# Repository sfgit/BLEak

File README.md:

BLEak
=====

BLE + ATMega Kit

Meet BLEak - the BLE + ATMega Kit.  This is a board I'm building for a one-day workshop in San Francisco.  The board includes the NRF8001 + ATMega328-AUR (SMD, a'la Arduino SMD) and should include some basic SPI sensors / IO.  Existing Arduino SW libraries for the nrf8001 should work with BLEak.  The basis of the workshop is to show the transition from Arduino to a production PCB and BLEak is a nice narrative that mixes some simple wireless / RF with the ATMega in a module that just might be the prodcut someone is trying to build.  

LICENSE + NOTES:  (PLEASE READ)
This design is released under a Creative-Commons Share-alike, Attribution license.  You can use this design without needing to ask for permission from me.

The designer (me, the guy typing this) is furnishing this item "as is". The design does not provide any warranty of the item whatsoever, whether express, implied, or statutory, including, but not limited to, any warranty of merchantability or fitness for a particular purpose or any warranty that the contents of the item will be error-free.

In no respect shall the designer incur any liability for any damages, including, but limited to, direct, indirect, special, or consequential damages arising out of, resulting from, or any way connected to the use of the item, whether or not based upon warranty, contract, tort, or otherwise; whether or not injury was sustained by persons or property or otherwise; and whether or not loss was sustained from, or arose out of, the results of, the item, or any services that may be provided by the designer.

Be careful.  This is a work in progress.  You use this AT YOUR OWN RISK.  Electronics such as these can kill.

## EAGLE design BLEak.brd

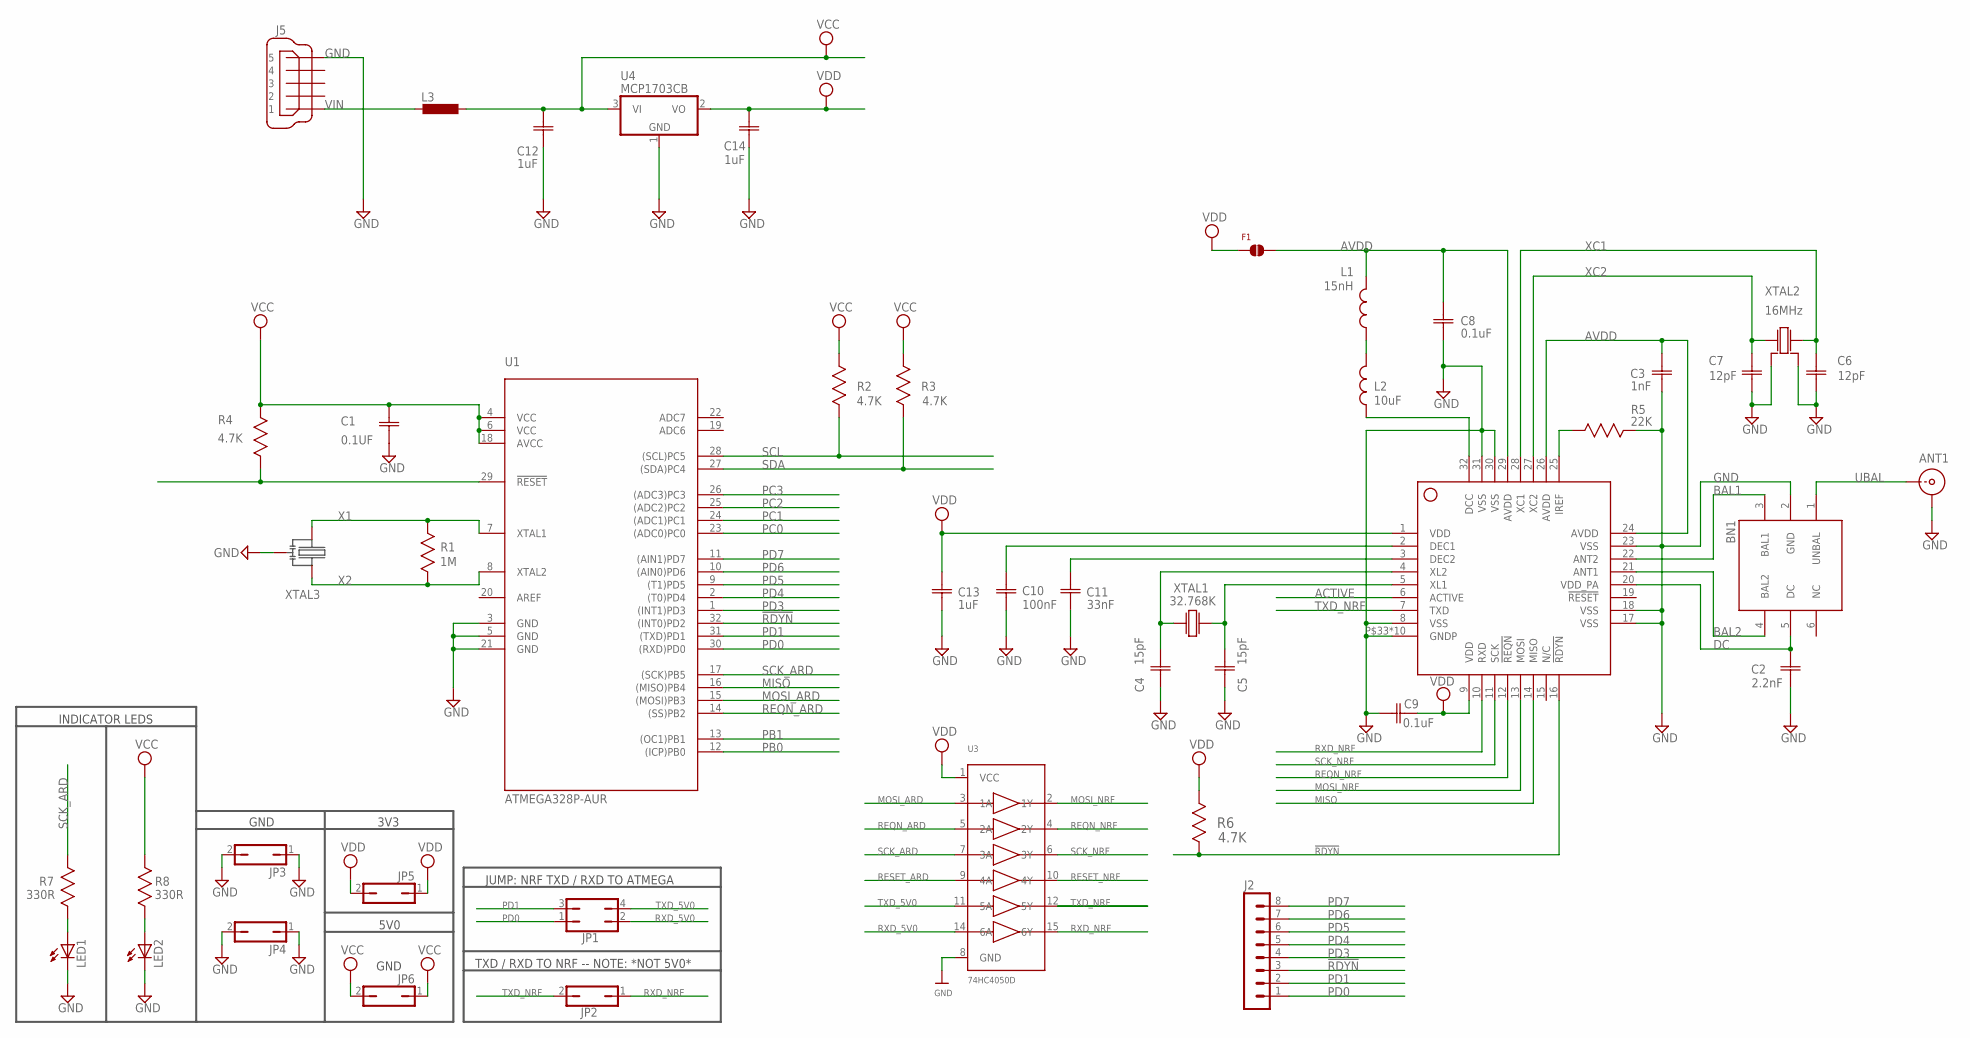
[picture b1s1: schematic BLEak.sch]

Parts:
ANT1: U.FL-R-SMT(01); U.FL; PARTNO U.FL-R-SMT(01)
BN1: 2450BM14A0002; BALUN; PARTNO 2450BM14A0002
C1: 0.1UF; CAPC1608X90N
C2: 2.2nF; CAPC1608X85N
C3: 1nF; CAPC1608X85N
C4, C5: 15pF; CAPC1608X85N
C6, C7: 12pF; CAPC1608X85N
C8, C9: 0.1uF; CAPC1608X90N
C10: 100nF; CAPC1608X90N
C11: 33nF; CAPC1608X85N
C12, C14: 1uF; CAPC2013X140N
C13: 1uF; CAPC1608X90N
F1: MMZ1608B121C; 0603
J2: MA08-1
J5: MINI-USB-UX60A-MB-5ST; UX60A-MB-5ST
JP1: JP2Q
JP2, JP3, JP4, JP5, JP6: JP1Q; JP1
L1: 15nH; 0402
L2: 10uF; 0603
L3: L-EUL1812; L1812
LED1, LED2: LEDCHIP-LED0603; CHIP-LED0603
R1: 1M; RESC1608X60N
R2, R3, R4, R6: 4.7K; RESC1608X60N
R5: 22K; RESC1608X60N
R7, R8: 330R; RESC1608X60N
U1: ATMEGA328P-AUR; TQFP-32; PARTNO ATMEGA328P-AUR
U2: NRF8001; QFN50P500X500X90-33N; PARTNO nRF8001
U3: 74HC4050D; TSSOP16
U4: MCP1703CB; SOT23
XTAL1: 32.768K; 3215
XTAL2: 16MHz; 3225
XTAL3: CSTCE16M0V53-R0

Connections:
!RDYN: J2.3, R6.2 (R2), U1.32 ((INT0)PD2), U2.16 (!RDYN)
ACTIVE: U2.6 (ACTIVE)
AVDD: C3.2 (C2), C8.2 (C2), F1.P$2 (2), L1.P$2, U2.24 (AVDD), U2.26 (AVDD), U2.29 (AVDD)
BAL1: BN1.3 (BAL1), U2.22 (ANT2)
BAL2: BN1.4 (BAL2), U2.21 (ANT1)
DC: BN1.5 (DC), C2.2 (C2), U2.20 (VDD_PA)
GND: ANT1.2, ANT1.3, BN1.2 (GND), C1.1 (C1), C2.1 (C1), C3.1 (C1), C4.1 (C1), C5.1 (C1), C6.1 (C1), C7.1 (C1), C8.1 (C1), C9.2 (C2), C10.1 (C1), C11.2 (C2), C12.1 (C1), C13.1 (C1), C14.1 (C1), J5.5, JP3.1, JP3.2, JP4.1, JP4.2, LED1.C, LED2.C, R5.1 (R1), U1.3 (GND), U1.5 (GND), U1.21 (GND), U2.8 (VSS), U2.17 (VSS), U2.18 (VSS), U2.23 (VSS), U2.30 (VSS), U2.31 (VSS), U2.P$33 (GNDP), U2.P$34 (GNDP), U2.P$35 (GNDP), U2.P$36 (GNDP), U2.P$37 (GNDP), U2.P$38 (GNDP), U2.P$39 (GNDP), U2.P$40 (GNDP), U2.P$41 (GNDP), U2.P$42 (GNDP), U3.8 (GND), U4.1 (GND), XTAL2.2, XTAL2.4, XTAL3.2
MISO: U1.16 ((MISO)PB4), U2.14 (MISO)
MOSI_ARD: U1.15 ((MOSI)PB3), U3.3 (1A)
MOSI_NRF: U2.13 (MOSI), U3.2 (1Y)
unnamed: R4.2 (R2), U1.29 (!RESET)
unnamed: R5.2 (R2), U2.25 (IREF)
unnamed: C4.2 (C2), U2.4 (XL2), XTAL1.2
unnamed: C5.2 (C2), U2.5 (XL1), XTAL1.1
unnamed: L1.P$1, L2.2
unnamed: L2.1, U2.32 (DCC)
unnamed: C11.1 (C1), U2.3 (DEC2)
unnamed: C10.2 (C2), U2.2 (DEC1)
unnamed: LED2.A, R8.2 (R2)
unnamed: LED1.A, R7.2 (R2)
PB0: U1.12 ((ICP)PB0)
PB1: U1.13 ((OC1)PB1)
PC0: U1.23 ((ADC0)PC0)
PC1: U1.24 ((ADC1)PC1)
PC2: U1.25 ((ADC2)PC2)
PC3: U1.26 ((ADC3)PC3)
PD0: J2.1, JP1.1, U1.30 ((RXD)PD0)
PD1: J2.2, JP1.3, U1.31 ((TXD)PD1)
PD3: J2.4, U1.1 ((INT1)PD3)
PD4: J2.5, U1.2 ((T0)PD4)
PD5: J2.6, U1.9 ((T1)PD5)
PD6: J2.7, U1.10 ((AIN0)PD6)
PD7: J2.8, U1.11 ((AIN1)PD7)
REQN_ARD: U3.5 (2A)
REQN_NRF: U2.12 (!REQN), U3.4 (2Y)
RESET_ARD: U3.9 (4A)
RESET_NRF: U3.10 (4Y)
RXD_5V0: JP1.2, U3.14 (6A)
RXD_NRF: JP2.1, U2.10 (RXD), U3.15 (6Y)
SCK_ARD: R7.1 (R1), U1.17 ((SCK)PB5), U3.7 (3A)
SCK_NRF: U2.11 (SCK), U3.6 (3Y)
SCL: R2.2 (R2), U1.28 ((SCL)PC5)
SDA: R3.2 (R2), U1.27 ((SDA)PC4)
TXD_5V0: JP1.4, U3.11 (5A)
TXD_NRF: JP2.2, U2.7 (TXD), U3.12 (5Y)
UBAL: ANT1.1, BN1.1 (UNBAL)
VCC: C1.2 (C2), C12.2 (C2), JP6.1, JP6.2, L3.1, R2.1 (R1), R3.1 (R1), R4.1 (R1), R8.1 (R1), U1.4 (VCC), U1.6 (VCC), U1.18 (AVCC), U4.3 (VI)
VDD: C9.1 (C1), C13.2 (C2), C14.2 (C2), F1.P$1 (1), JP5.1, JP5.2, R6.1 (R1), U2.1 (VDD), U2.9 (VDD), U3.1 (VCC), U4.2 (VO)
VIN: J5.1, L3.2
X1: R1.2 (R2), U1.7 (XTAL1), XTAL3.1
X2: R1.1 (R1), U1.8 (XTAL2), XTAL3.3
XC1: C6.2 (C2), U2.28 (XC1), XTAL2.3
XC2: C7.2 (C2), U2.27 (XC2), XTAL2.1

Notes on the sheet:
JUMP: NRF TXD / RXD TO ATMEGA
TXD / RXD TO NRF -- NOTE: *NOT 5V0*
GND
3V3
5V0
INDICATOR LEDS

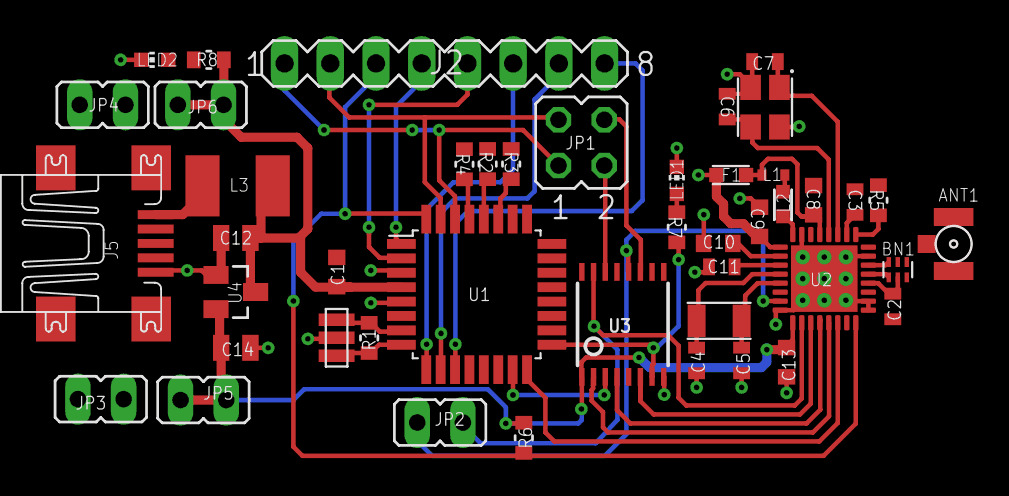
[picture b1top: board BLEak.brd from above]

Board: 2 copper layers, 45 parts (0 on the bottom side), 43 nets.

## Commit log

2014-10-20 Initial Commit
    First commit - work in progress

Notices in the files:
parts and their libraries:
microbuilder: This work is placed in the public domain, and may be freely used for commercial and non-commercial work with the following conditions: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
